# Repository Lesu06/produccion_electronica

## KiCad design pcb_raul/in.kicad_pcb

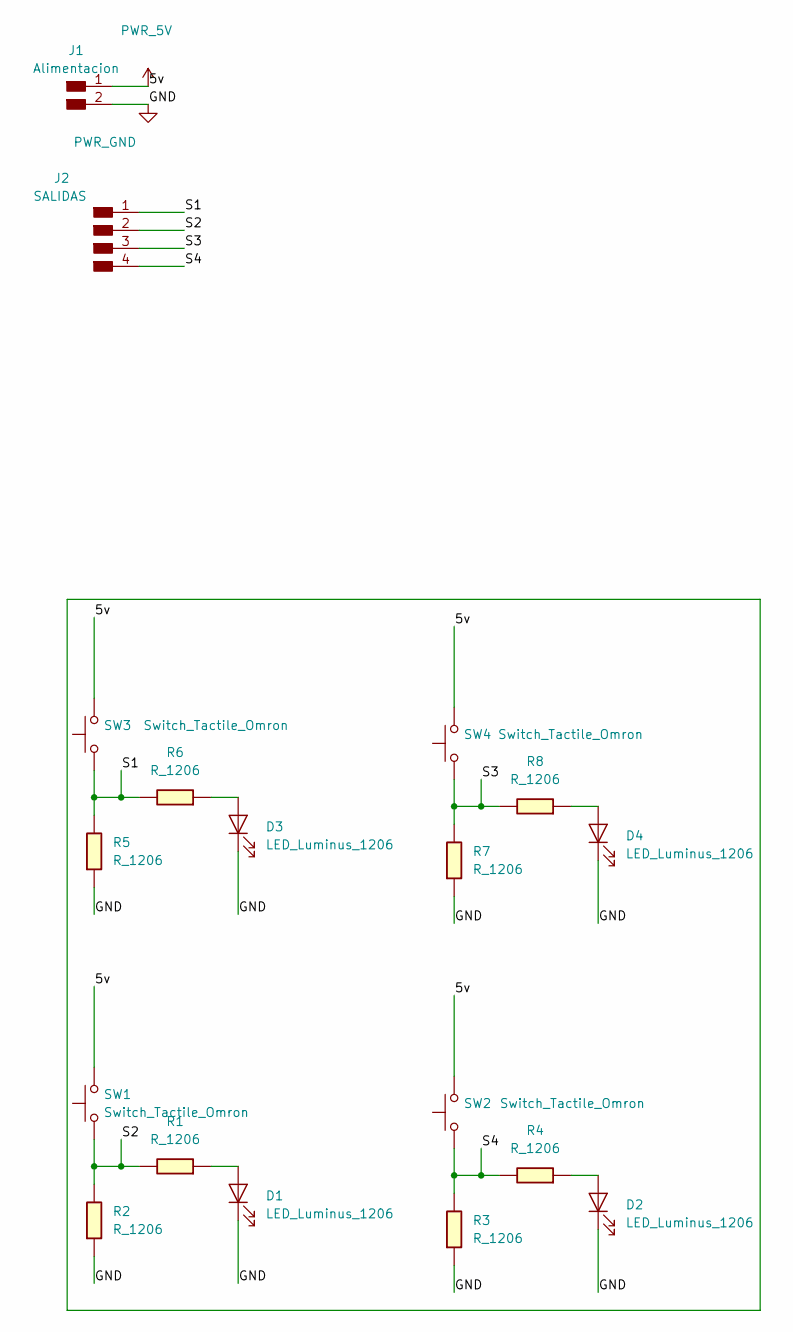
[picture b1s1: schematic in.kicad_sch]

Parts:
D1, D2, D3, D4: LED_Luminus_1206
J1: Alimentacion; PinHeader_1x02_P2.54mm_Vertical_THT_D1.4mm
J2: SALIDAS; PinHeader_1x04_P2.54mm_Vertical_THT_D1.4mm
R1, R2, R3, R4, R5, R6, R7, R8: R_1206
SW1, SW2, SW3, SW4: Switch_Tactile_Omron; Button_Omron_B3SN_6.0x6.0mm

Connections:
/S1: J2.1, R5.1, R6.1, SW3.1
/S2: J2.2, R1.1, R2.1, SW1.1
/S3: J2.3, R7.1, R8.1, SW4.1
/S4: J2.4, R3.1, R4.1, SW2.1
unnamed: D1.2 (A), R1.2
unnamed: D2.2 (A), R4.2
unnamed: D3.2 (A), R6.2
unnamed: D4.2 (A), R8.2
PWR_5V: J1.1, SW1.2, SW2.2, SW3.2, SW4.2
PWR_GND: D1.1 (K), D2.1 (K), D3.1 (K), D4.1 (K), J1.2, R2.2, R3.2, R5.2, R7.2

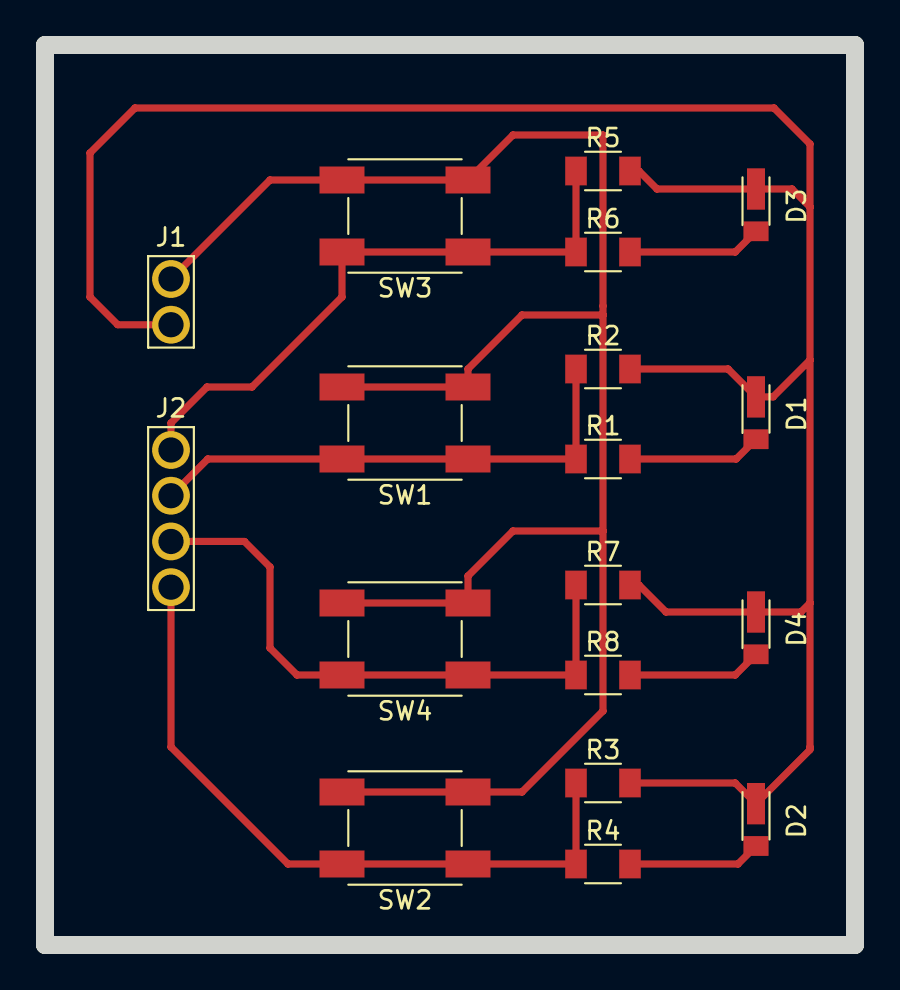
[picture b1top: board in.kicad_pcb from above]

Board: 2 copper layers, 45.0 x 50.0 mm, 18 parts (0 on the bottom side), 10 nets.
